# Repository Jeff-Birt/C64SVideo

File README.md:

## Mk3 SVideo cable for the C64/C128

The Mk1 version was simple a low quality SVideo cable and stereo audio cable soldered to an 8-pin DIN plug. This was usable but had shortcomings, notably lack of a 330ohm resistor for the chroma signal and the whine from the SID audio input.

The Mk2 version was done in a hurray to overcome the annoying whine of the SID's audio input picking up noise. Though it was supposed to be a temporary solution it lasted a few years with a lot of patching back together.

The Mk3 cable was made with mostly things I had on hand and using the proper type of shielded cables. While a bit fiddly to build because of the tiny VGA cable wires it works very well. I milled out the PCB I used (C64_SVideo_Cable_Milled_2021-02-28.zip) but also created a version that can be professionally made by PCBWay, etc. (C64_SVideo_Cable_Pro_2021-03-17.zip). I have not had any of these PCBs made but they should be OK.  

See the Mk3_C64_SVideo_Cable_BOM.xlsx file for the BOM.

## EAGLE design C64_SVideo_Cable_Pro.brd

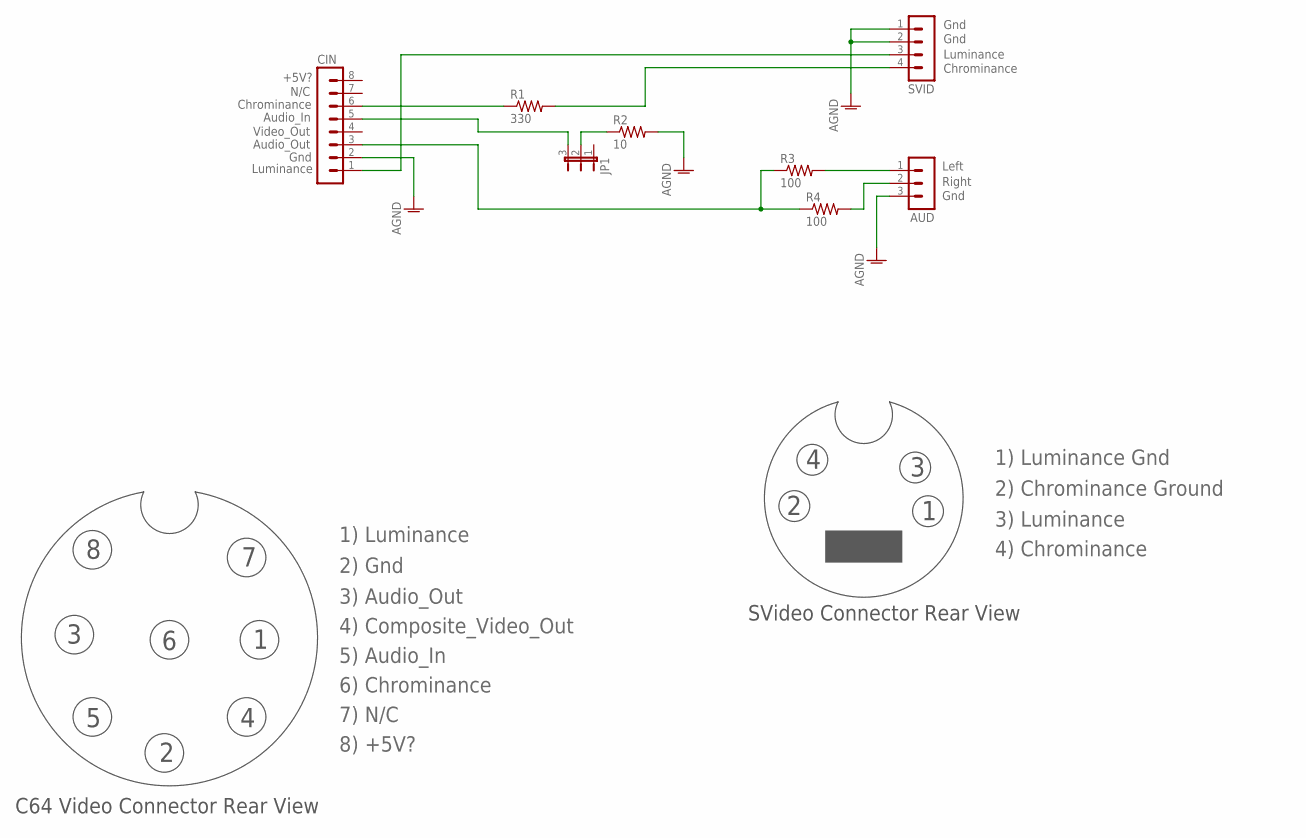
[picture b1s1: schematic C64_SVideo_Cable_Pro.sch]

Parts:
AUD: MA03-1
CIN: MA08-1
JP1: JP2E; JP2
R1: 330; 0309/12
R2: 10; 0309/12
R3, R4: 100; 0309/12
SVID: MA04-1

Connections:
AGND: AUD.3, CIN.2, R2.2, SVID.1, SVID.2
unnamed: CIN.6, R1.1
unnamed: R1.2, SVID.4
unnamed: AUD.1, R3.2
unnamed: AUD.2, R4.2
unnamed: CIN.5, JP1.3
unnamed: JP1.2, R2.1
unnamed: CIN.3, R3.1, R4.1
unnamed: CIN.1, SVID.3

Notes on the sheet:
Luminance
Gnd
Audio_Out
Video_Out
Audio_In
Chrominance
+5V?
N/C
Left
Right
1) Luminance
2) Gnd
3) Audio_Out
4) Composite_Video_Out
5) Audio_In
6) Chrominance
8) +5V?
7) N/C
C64 Video Connector Rear View
SVideo Connector Rear View
1) Luminance Gnd
2) Chrominance Ground
3) Luminance
4) Chrominance

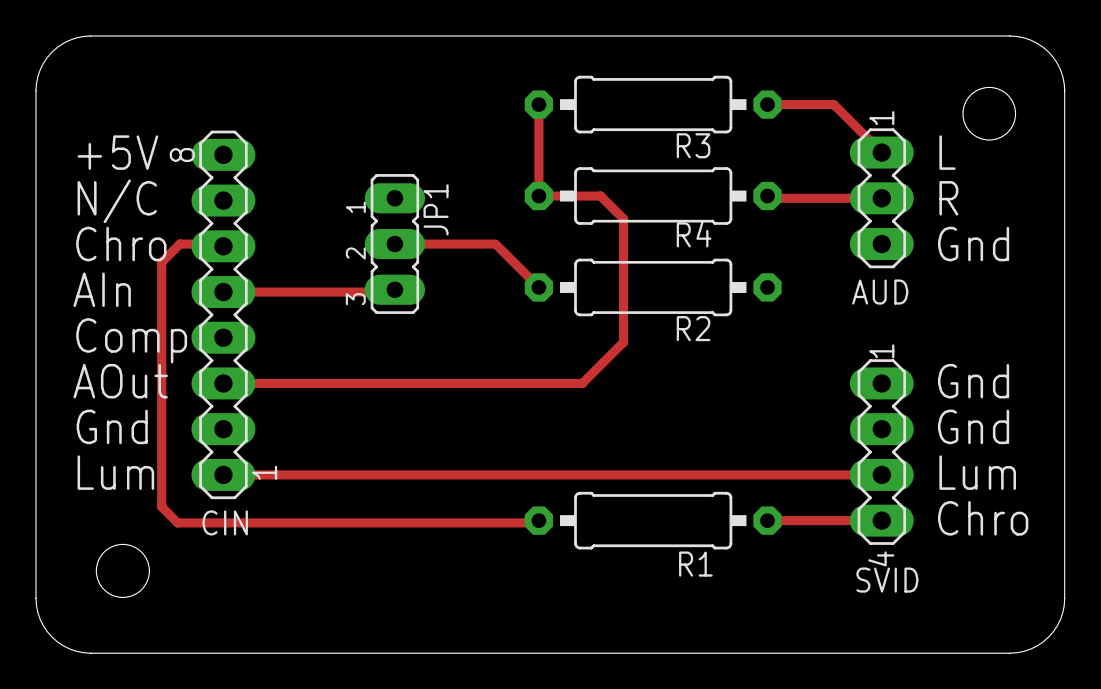
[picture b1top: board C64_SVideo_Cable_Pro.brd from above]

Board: 2 copper layers, 57.1 x 34.3 mm, 8 parts (0 on the bottom side), 9 nets.

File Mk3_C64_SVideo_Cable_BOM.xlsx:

Designation | Description | Value | Link
R1 | 1/4 watt carbon resistor | 330 ohm
R2 | 1/4 watt carbon resistor | 10-100 ohm
R3 | 1/4 watt carbon resistor | 10-100 ohm
R4 | 1/4 watt carbon resistor | 10-100 ohm
JP1 | 3 position header or jumper wire
PCB1 | PCB, milled out or pro made
VGA1 | section of VGA cable
SVideo1 | Svideo cable, one end cut off | 25-235-006 | https://www.showmecables.com/premium-gold-plated-s-video-cable-6-ft
DIN 8-pin | 8-pin C64 video connector | SOI-8PINDIN-M | https://www.soigeneris.com/commodore-64-8-pin-round-din-conn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
Enc1 | Enclsoure | Bud HB-3465 | https://www.budind.com/pdf/hb3465.pdf

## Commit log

2021-03-17 Initial commit
    Added design files and BOM
